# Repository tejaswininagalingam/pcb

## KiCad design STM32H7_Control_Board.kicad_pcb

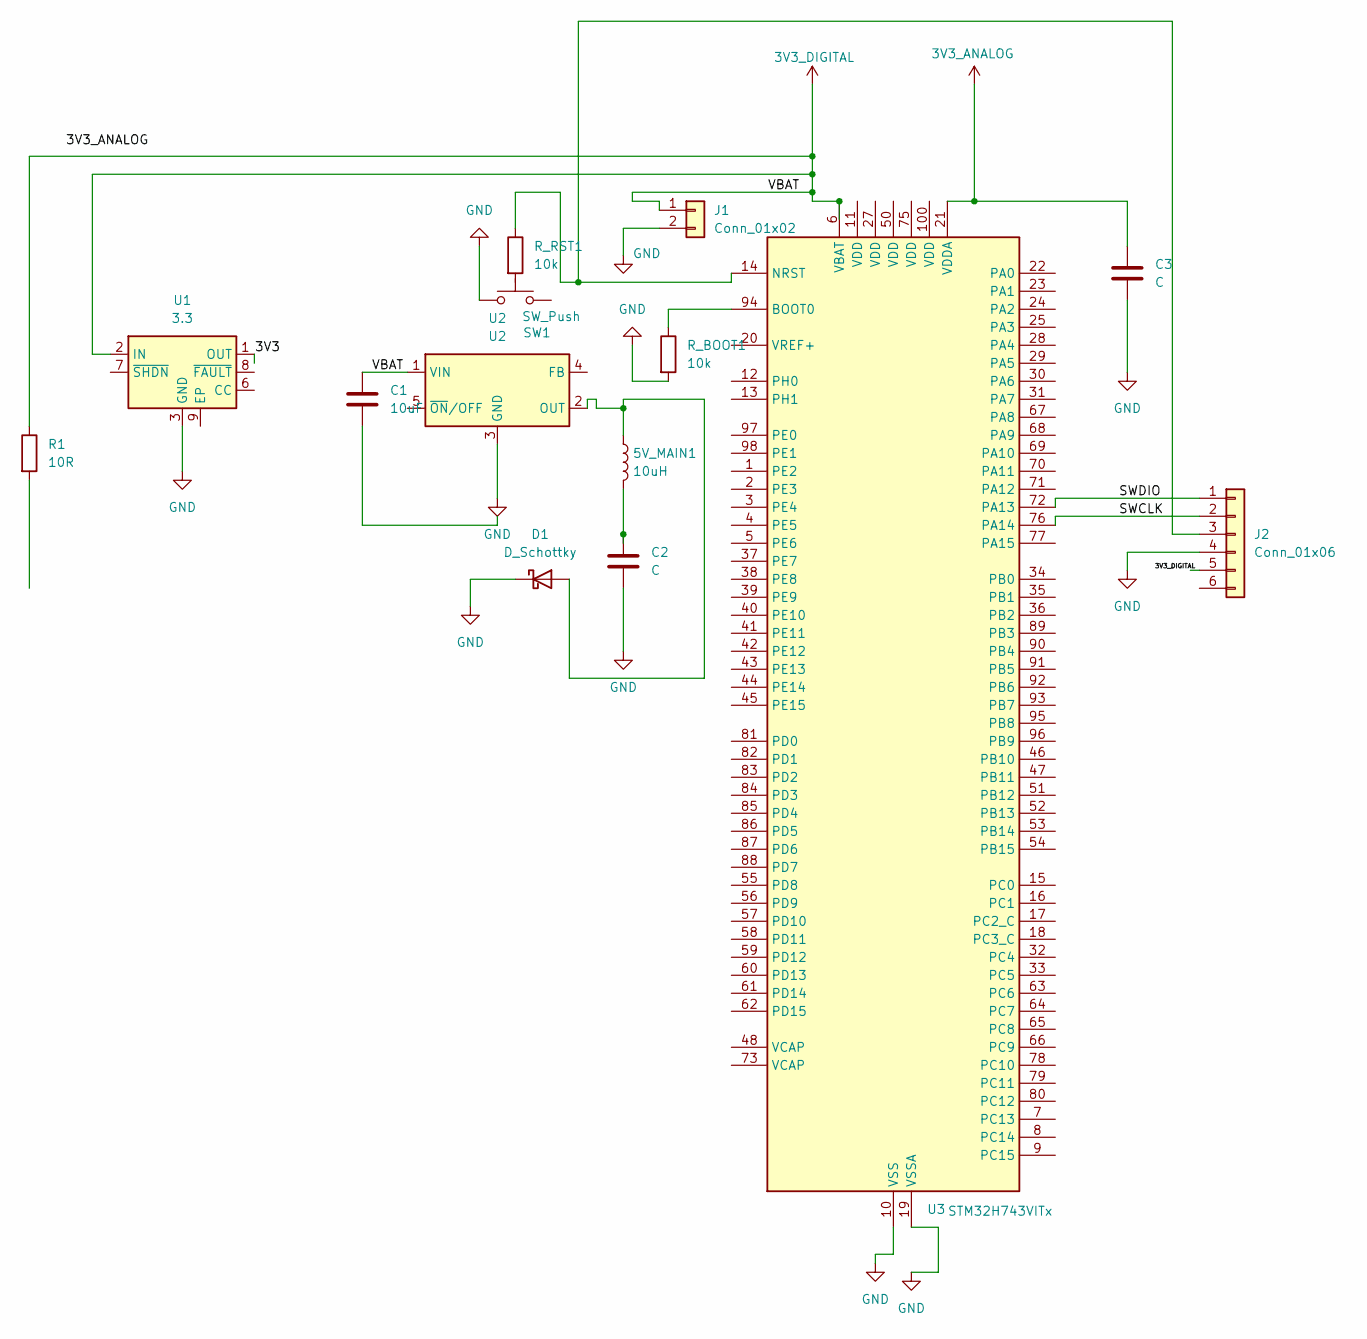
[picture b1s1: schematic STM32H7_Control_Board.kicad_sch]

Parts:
5V_MAIN1: 10uH; L_0805_2012Metric_Pad1.05x1.20mm_HandSolder
C1: 10uF; PinHeader_1x02_P2.54mm_Vertical
C2, C3: C; PinHeader_1x02_P2.54mm_Vertical
D1: D_Schottky; D_SOD-123
J1: Conn_01x02; PinHeader_1x02_P2.54mm_Vertical
J2: Conn_01x06; PinHeader_1x06_P2.54mm_Vertical
R1: 10R; R_0603_1608Metric
R_BOOT1: 10k; R_0603_1608Metric
R_RST1: 10k; R_0603_1608Metric
SW1: SW_Push; SW_SPST_TL3342
U1: 3.3; WSON-8-1EP_3x2.5mm_P0.5mm_EP1.2x1.5mm_PullBack_ThermalVias
U2: U2; TO-263-5_TabPin3
U3: STM32H743VITx; LQFP-100_14x14mm_P0.5mm

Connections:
3V3_ANALOG: C3.1, U3.21 (VDDA)
3V3_DIGITAL: C1.1, J1.1, R1.1, U1.2 (IN), U2.1 (VIN), U3.6 (VBAT)
/3V3: U1.1 (OUT), U1.4 (OUT)
/SWCLK: J2.2, U3.76 (PA14)
/SWDIO: J2.1, U3.72 (PA13)
GND: C2.2, C3.2, D1.1 (K), J1.2, J2.4, R_BOOT1.2, SW1.1, U1.3 (GND), U2.3 (GND), U3.10 (VSS), U3.19 (VSSA), U3.26 (VSS), U3.49 (VSS), U3.74 (VSS), U3.99 (VSS)
unnamed: 5V_MAIN1.2, C2.1
unnamed: 5V_MAIN1.1, D1.2 (A), U2.2 (OUT)
unnamed: J2.3, R_RST1.1, U3.14 (NRST)
unnamed: R_BOOT1.1, U3.94 (BOOT0)

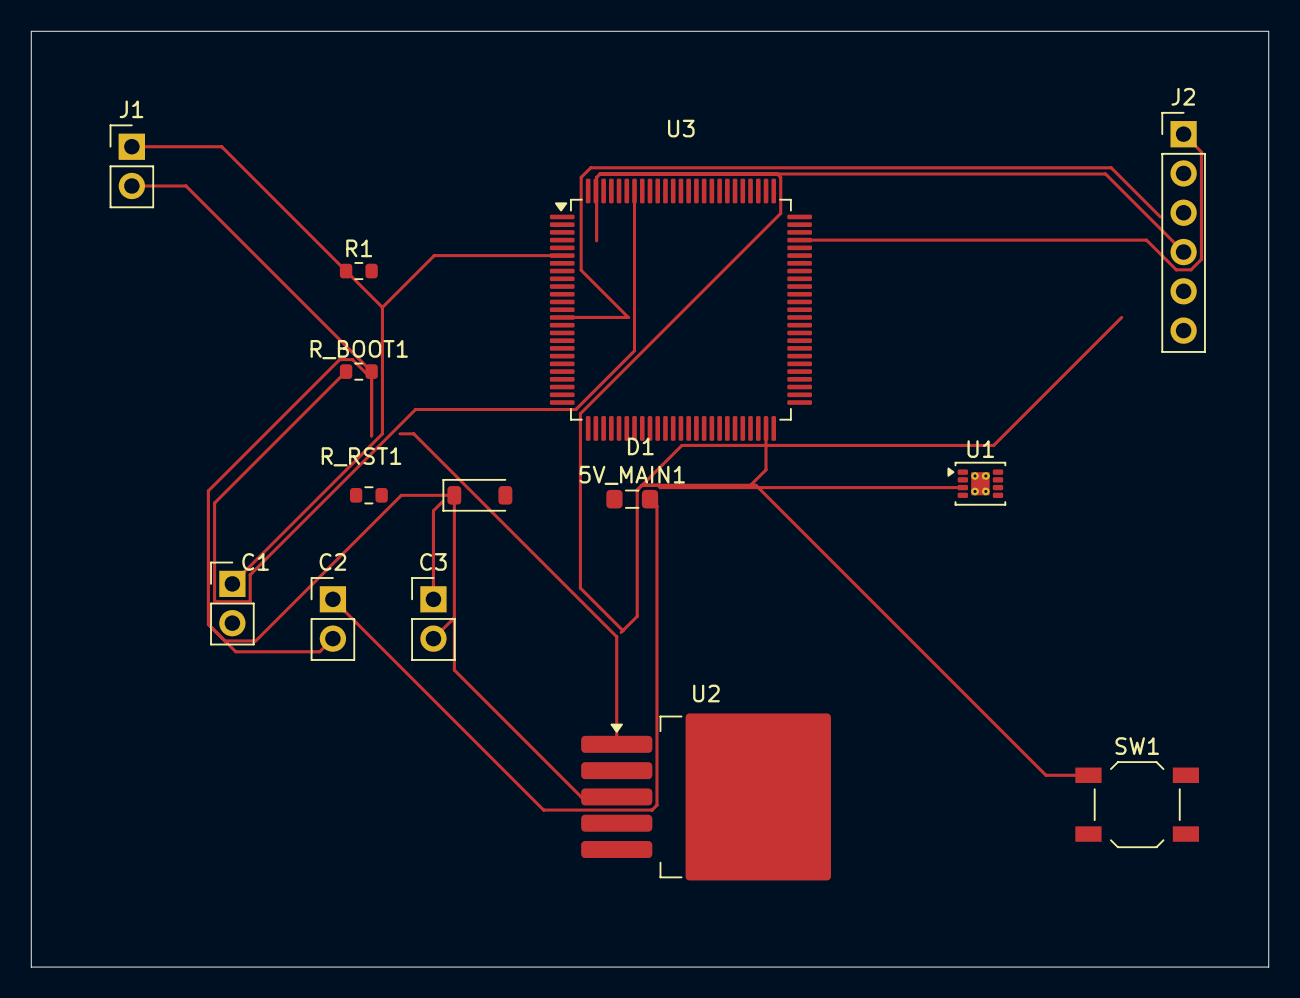
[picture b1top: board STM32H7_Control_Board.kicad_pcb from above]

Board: 2 copper layers, 80.0 x 60.5 mm, 14 parts (0 on the bottom side), 10 nets.
